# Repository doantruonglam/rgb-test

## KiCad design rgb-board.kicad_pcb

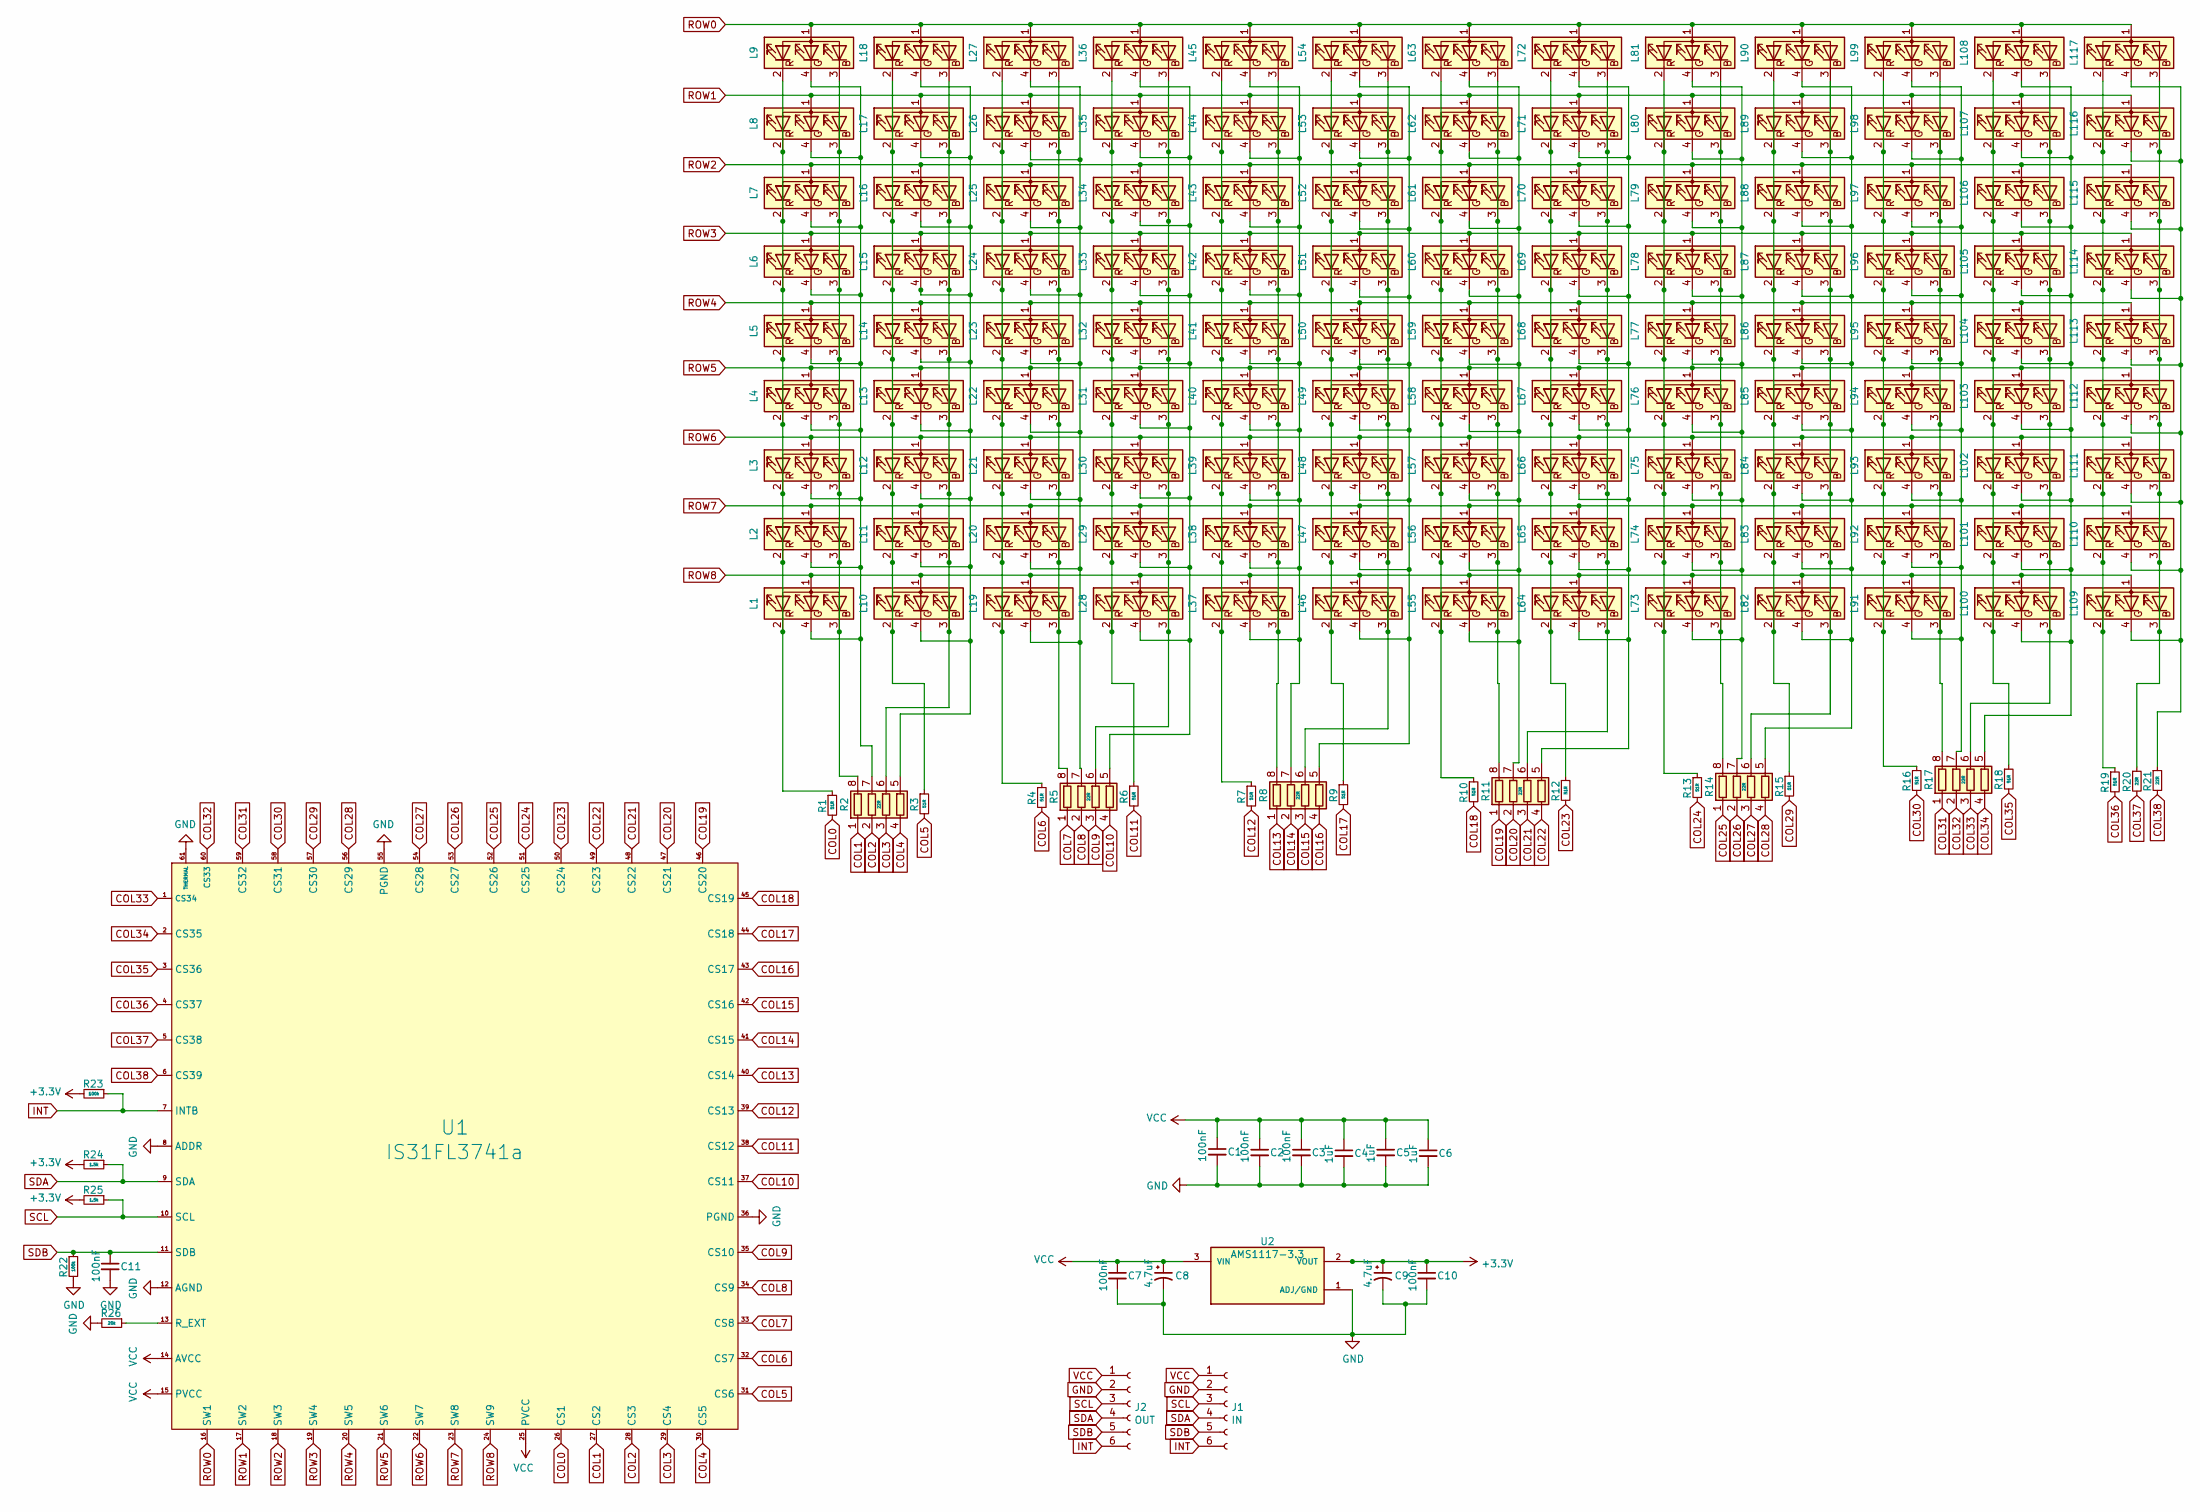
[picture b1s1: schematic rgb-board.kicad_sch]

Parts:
C1, C2, C3, C7, C10, C11: 100nF; C_0805_2012Metric
C4, C5, C6: 1uF; C_0805_2012Metric
C8, C9: 4.7uF; C_0805_2012Metric
J1: IN; PinHeader_1x06_P1.00mm_Vertical
J2: OUT; PinHeader_1x06_P1.00mm_Vertical
L1, L2, L3, L4, L5, L6, L7, L8, L9, L10, L11, L12, L13, L14, L15, L16, L17, L18, L19, L20, L21, L22, L23, L24, L25, L26, L27, L28, L29, L30, L31, L32, L33, L34, L35, L36, L37, L38, L39, L40, L41, L42, L43, L44, L45, L46, L47, L48, L49, L50, L51, L52, L53, L54, L55, L56, L57, L58, L59, L60, L61, L62, L63, L64, L65, L66, L67, L68, L69, L70, L71, L72, L73, L74, L75, L76, L77, L78, L79, L80, L81, L82, L83, L84, L85, L86, L87, L88, L89, L90, L91, L92, L93, L94, L95, L96, L97, L98, L99, L100, L101, L102, L103, L104, L105, L106, L107, L108, L109, L110, L111, L112, L113, L114, L115, L116, L117: LED_ARBG; DIOSC160X150X35-4N
R1, R3, R4, R6, R7, R9, R10, R12, R13, R15, R16, R18, R19: 51R; R_0603_1608Metric
R2, R5, R8, R11, R14, R17: 22R; R_Array_Convex_4x0603
R20, R21: 22R; R_0603_1608Metric
R22, R23: 100k; R_0603_1608Metric
R24, R25: 1.5k; R_0603_1608Metric
R26: 20k; R_0603_1608Metric
U1: IS31FL3741a; QFN-60-1EP_7x7mm_P0.4mm_EP5.4x5.4mm_ThermalReliefs; Manufacturer Part Number IS31FL3741A
U2: AMS1117-3.3; SOT-223-3_TabPin2

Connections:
+3V3: C9.1, C10.1, R23.2, R24.2, R25.2, U2.2 (VOUT)
COL0: R1.2, U1.26 (CS1)
COL1: R2.1 (R1.1), U1.27 (CS2)
COL2: R2.2 (R2.1), U1.28 (CS3)
COL3: R2.3 (R3.1), U1.29 (CS4)
COL4: R2.4 (R4.1), U1.30 (CS5)
COL5: R3.2, U1.31 (CS6)
COL6: R4.2, U1.32 (CS7)
COL7: R5.1 (R1.1), U1.33 (CS8)
COL8: R5.2 (R2.1), U1.34 (CS9)
COL9: R5.3 (R3.1), U1.35 (CS10)
COL10: R5.4 (R4.1), U1.37 (CS11)
COL11: R6.2, U1.38 (CS12)
COL12: R7.2, U1.39 (CS13)
COL13: R8.1 (R1.1), U1.40 (CS14)
COL14: R8.2 (R2.1), U1.41 (CS15)
COL15: R8.3 (R3.1), U1.42 (CS16)
COL16: R8.4 (R4.1), U1.43 (CS17)
COL17: R9.2, U1.44 (CS18)
COL18: R10.2, U1.45 (CS19)
COL19: R11.1 (R1.1), U1.46 (CS20)
COL20: R11.2 (R2.1), U1.47 (CS21)
COL21: R11.3 (R3.1), U1.48 (CS22)
COL22: R11.4 (R4.1), U1.49 (CS23)
COL23: R12.2, U1.50 (CS24)
COL24: R13.2, U1.51 (CS25)
COL25: R14.1 (R1.1), U1.52 (CS26)
COL26: R14.2 (R2.1), U1.53 (CS27)
COL27: R14.3 (R3.1), U1.54 (CS28)
COL28: R14.4 (R4.1), U1.56 (CS29)
COL29: R15.2, U1.57 (CS30)
COL30: R16.2, U1.58 (CS31)
COL31: R17.1 (R1.1), U1.59 (CS32)
COL32: R17.2 (R2.1), U1.60 (CS33)
COL33: R17.3 (R3.1), U1.1 (CS34)
COL34: R17.4 (R4.1), U1.2 (CS35)
COL35: R18.2, U1.3 (CS36)
COL36: R19.2, U1.4 (CS37)
COL37: R20.2, U1.5 (CS38)
COL38: R21.2, U1.6 (CS39)
GND: C1.2, C2.2, C3.2, C4.2, C5.2, C6.2, C7.2, C8.2, C9.2, C10.2, C11.2, J1.2, J2.2, R22.2, R26.2, U1.8 (ADDR), U1.12 (AGND), U1.36 (PGND), U1.55 (PGND), U1.61 (THERMAL), U2.1 (ADJ/GND)
INT: J1.6, J2.6, R23.1, U1.7 (INTB)
unnamed: L1.2 (RK), L2.2 (RK), L3.2 (RK), L4.2 (RK), L5.2 (RK), L6.2 (RK), L7.2 (RK), L8.2 (RK), L9.2 (RK), R1.1
unnamed: L1.3 (BK), L2.3 (BK), L3.3 (BK), L4.3 (BK), L5.3 (BK), L6.3 (BK), L7.3 (BK), L8.3 (BK), L9.3 (BK), R2.8 (R1.2)
unnamed: L1.4 (GK), L2.4 (GK), L3.4 (GK), L4.4 (GK), L5.4 (GK), L6.4 (GK), L7.4 (GK), L8.4 (GK), L9.4 (GK), R2.7 (R2.2)
unnamed: L10.2 (RK), L11.2 (RK), L12.2 (RK), L13.2 (RK), L14.2 (RK), L15.2 (RK), L16.2 (RK), L17.2 (RK), L18.2 (RK), R3.1
unnamed: L10.3 (BK), L11.3 (BK), L12.3 (BK), L13.3 (BK), L14.3 (BK), L15.3 (BK), L16.3 (BK), L17.3 (BK), L18.3 (BK), R2.6 (R3.2)
unnamed: L10.4 (GK), L11.4 (GK), L12.4 (GK), L13.4 (GK), L14.4 (GK), L15.4 (GK), L16.4 (GK), L17.4 (GK), L18.4 (GK), R2.5 (R4.2)
unnamed: L19.2 (RK), L20.2 (RK), L21.2 (RK), L22.2 (RK), L23.2 (RK), L24.2 (RK), L25.2 (RK), L26.2 (RK), L27.2 (RK), R4.1
unnamed: L19.3 (BK), L20.3 (BK), L21.3 (BK), L22.3 (BK), L23.3 (BK), L24.3 (BK), L25.3 (BK), L26.3 (BK), L27.3 (BK), R5.8 (R1.2)
unnamed: L19.4 (GK), L20.4 (GK), L21.4 (GK), L22.4 (GK), L23.4 (GK), L24.4 (GK), L25.4 (GK), L26.4 (GK), L27.4 (GK), R5.7 (R2.2)
unnamed: L28.2 (RK), L29.2 (RK), L30.2 (RK), L31.2 (RK), L32.2 (RK), L33.2 (RK), L34.2 (RK), L35.2 (RK), L36.2 (RK), R6.1
unnamed: L28.3 (BK), L29.3 (BK), L30.3 (BK), L31.3 (BK), L32.3 (BK), L33.3 (BK), L34.3 (BK), L35.3 (BK), L36.3 (BK), R5.6 (R3.2)
unnamed: L28.4 (GK), L29.4 (GK), L30.4 (GK), L31.4 (GK), L32.4 (GK), L33.4 (GK), L34.4 (GK), L35.4 (GK), L36.4 (GK), R5.5 (R4.2)
unnamed: L37.2 (RK), L38.2 (RK), L39.2 (RK), L40.2 (RK), L41.2 (RK), L42.2 (RK), L43.2 (RK), L44.2 (RK), L45.2 (RK), R7.1
unnamed: L37.3 (BK), L38.3 (BK), L39.3 (BK), L40.3 (BK), L41.3 (BK), L42.3 (BK), L43.3 (BK), L44.3 (BK), L45.3 (BK), R8.8 (R1.2)
unnamed: L37.4 (GK), L38.4 (GK), L39.4 (GK), L40.4 (GK), L41.4 (GK), L42.4 (GK), L43.4 (GK), L44.4 (GK), L45.4 (GK), R8.7 (R2.2)
unnamed: L46.2 (RK), L47.2 (RK), L48.2 (RK), L49.2 (RK), L50.2 (RK), L51.2 (RK), L52.2 (RK), L53.2 (RK), L54.2 (RK), R9.1
unnamed: L46.3 (BK), L47.3 (BK), L48.3 (BK), L49.3 (BK), L50.3 (BK), L51.3 (BK), L52.3 (BK), L53.3 (BK), L54.3 (BK), R8.6 (R3.2)
unnamed: L46.4 (GK), L47.4 (GK), L48.4 (GK), L49.4 (GK), L50.4 (GK), L51.4 (GK), L52.4 (GK), L53.4 (GK), L54.4 (GK), R8.5 (R4.2)
unnamed: L55.2 (RK), L56.2 (RK), L57.2 (RK), L58.2 (RK), L59.2 (RK), L60.2 (RK), L61.2 (RK), L62.2 (RK), L63.2 (RK), R10.1
unnamed: L55.3 (BK), L56.3 (BK), L57.3 (BK), L58.3 (BK), L59.3 (BK), L60.3 (BK), L61.3 (BK), L62.3 (BK), L63.3 (BK), R11.8 (R1.2)
unnamed: L55.4 (GK), L56.4 (GK), L57.4 (GK), L58.4 (GK), L59.4 (GK), L60.4 (GK), L61.4 (GK), L62.4 (GK), L63.4 (GK), R11.7 (R2.2)
unnamed: L64.2 (RK), L65.2 (RK), L66.2 (RK), L67.2 (RK), L68.2 (RK), L69.2 (RK), L70.2 (RK), L71.2 (RK), L72.2 (RK), R12.1
unnamed: L64.3 (BK), L65.3 (BK), L66.3 (BK), L67.3 (BK), L68.3 (BK), L69.3 (BK), L70.3 (BK), L71.3 (BK), L72.3 (BK), R11.6 (R3.2)
unnamed: L64.4 (GK), L65.4 (GK), L66.4 (GK), L67.4 (GK), L68.4 (GK), L69.4 (GK), L70.4 (GK), L71.4 (GK), L72.4 (GK), R11.5 (R4.2)
unnamed: L73.2 (RK), L74.2 (RK), L75.2 (RK), L76.2 (RK), L77.2 (RK), L78.2 (RK), L79.2 (RK), L80.2 (RK), L81.2 (RK), R13.1
unnamed: L73.3 (BK), L74.3 (BK), L75.3 (BK), L76.3 (BK), L77.3 (BK), L78.3 (BK), L79.3 (BK), L80.3 (BK), L81.3 (BK), R14.8 (R1.2)
unnamed: L73.4 (GK), L74.4 (GK), L75.4 (GK), L76.4 (GK), L77.4 (GK), L78.4 (GK), L79.4 (GK), L80.4 (GK), L81.4 (GK), R14.7 (R2.2)
unnamed: L82.2 (RK), L83.2 (RK), L84.2 (RK), L85.2 (RK), L86.2 (RK), L87.2 (RK), L88.2 (RK), L89.2 (RK), L90.2 (RK), R15.1
unnamed: L82.3 (BK), L83.3 (BK), L84.3 (BK), L85.3 (BK), L86.3 (BK), L87.3 (BK), L88.3 (BK), L89.3 (BK), L90.3 (BK), R14.6 (R3.2)
unnamed: L82.4 (GK), L83.4 (GK), L84.4 (GK), L85.4 (GK), L86.4 (GK), L87.4 (GK), L88.4 (GK), L89.4 (GK), L90.4 (GK), R14.5 (R4.2)
unnamed: L91.2 (RK), L92.2 (RK), L93.2 (RK), L94.2 (RK), L95.2 (RK), L96.2 (RK), L97.2 (RK), L98.2 (RK), L99.2 (RK), R16.1
unnamed: L91.3 (BK), L92.3 (BK), L93.3 (BK), L94.3 (BK), L95.3 (BK), L96.3 (BK), L97.3 (BK), L98.3 (BK), L99.3 (BK), R17.8 (R1.2)
unnamed: L91.4 (GK), L92.4 (GK), L93.4 (GK), L94.4 (GK), L95.4 (GK), L96.4 (GK), L97.4 (GK), L98.4 (GK), L99.4 (GK), R17.7 (R2.2)
unnamed: L100.2 (RK), L101.2 (RK), L102.2 (RK), L103.2 (RK), L104.2 (RK), L105.2 (RK), L106.2 (RK), L107.2 (RK), L108.2 (RK), R18.1
unnamed: L100.3 (BK), L101.3 (BK), L102.3 (BK), L103.3 (BK), L104.3 (BK), L105.3 (BK), L106.3 (BK), L107.3 (BK), L108.3 (BK), R17.6 (R3.2)
unnamed: L100.4 (GK), L101.4 (GK), L102.4 (GK), L103.4 (GK), L104.4 (GK), L105.4 (GK), L106.4 (GK), L107.4 (GK), L108.4 (GK), R17.5 (R4.2)
unnamed: L109.2 (RK), L110.2 (RK), L111.2 (RK), L112.2 (RK), L113.2 (RK), L114.2 (RK), L115.2 (RK), L116.2 (RK), L117.2 (RK), R19.1
unnamed: L109.3 (BK), L110.3 (BK), L111.3 (BK), L112.3 (BK), L113.3 (BK), L114.3 (BK), L115.3 (BK), L116.3 (BK), L117.3 (BK), R20.1
unnamed: L109.4 (GK), L110.4 (GK), L111.4 (GK), L112.4 (GK), L113.4 (GK), L114.4 (GK), L115.4 (GK), L116.4 (GK), L117.4 (GK), R21.1
unnamed: R26.1, U1.13 (R_EXT)
ROW0: L9.1 (A), L18.1 (A), L27.1 (A), L36.1 (A), L45.1 (A), L54.1 (A), L63.1 (A), L72.1 (A), L81.1 (A), L90.1 (A), L99.1 (A), L108.1 (A), L117.1 (A), U1.16 (SW1)
ROW1: L8.1 (A), L17.1 (A), L26.1 (A), L35.1 (A), L44.1 (A), L53.1 (A), L62.1 (A), L71.1 (A), L80.1 (A), L89.1 (A), L98.1 (A), L107.1 (A), L116.1 (A), U1.17 (SW2)
ROW2: L7.1 (A), L16.1 (A), L25.1 (A), L34.1 (A), L43.1 (A), L52.1 (A), L61.1 (A), L70.1 (A), L79.1 (A), L88.1 (A), L97.1 (A), L106.1 (A), L115.1 (A), U1.18 (SW3)
ROW3: L6.1 (A), L15.1 (A), L24.1 (A), L33.1 (A), L42.1 (A), L51.1 (A), L60.1 (A), L69.1 (A), L78.1 (A), L87.1 (A), L96.1 (A), L105.1 (A), L114.1 (A), U1.19 (SW4)
ROW4: L5.1 (A), L14.1 (A), L23.1 (A), L32.1 (A), L41.1 (A), L50.1 (A), L59.1 (A), L68.1 (A), L77.1 (A), L86.1 (A), L95.1 (A), L104.1 (A), L113.1 (A), U1.20 (SW5)
ROW5: L4.1 (A), L13.1 (A), L22.1 (A), L31.1 (A), L40.1 (A), L49.1 (A), L58.1 (A), L67.1 (A), L76.1 (A), L85.1 (A), L94.1 (A), L103.1 (A), L112.1 (A), U1.21 (SW6)
ROW6: L3.1 (A), L12.1 (A), L21.1 (A), L30.1 (A), L39.1 (A), L48.1 (A), L57.1 (A), L66.1 (A), L75.1 (A), L84.1 (A), L93.1 (A), L102.1 (A), L111.1 (A), U1.22 (SW7)
ROW7: L2.1 (A), L11.1 (A), L20.1 (A), L29.1 (A), L38.1 (A), L47.1 (A), L56.1 (A), L65.1 (A), L74.1 (A), L83.1 (A), L92.1 (A), L101.1 (A), L110.1 (A), U1.23 (SW8)
ROW8: L1.1 (A), L10.1 (A), L19.1 (A), L28.1 (A), L37.1 (A), L46.1 (A), L55.1 (A), L64.1 (A), L73.1 (A), L82.1 (A), L91.1 (A), L100.1 (A), L109.1 (A), U1.24 (SW9)
SCL: J1.3, J2.3, R25.1, U1.10 (SCL)
SDA: J1.4, J2.4, R24.1, U1.9 (SDA)
SDB: C11.1, J1.5, J2.5, R22.1, U1.11 (SDB)
VCC: C1.1, C2.1, C3.1, C4.1, C5.1, C6.1, C7.1, C8.1, J1.1, J2.1, U1.14 (AVCC), U1.15 (PVCC), U1.25 (PVCC), U2.3 (VIN)

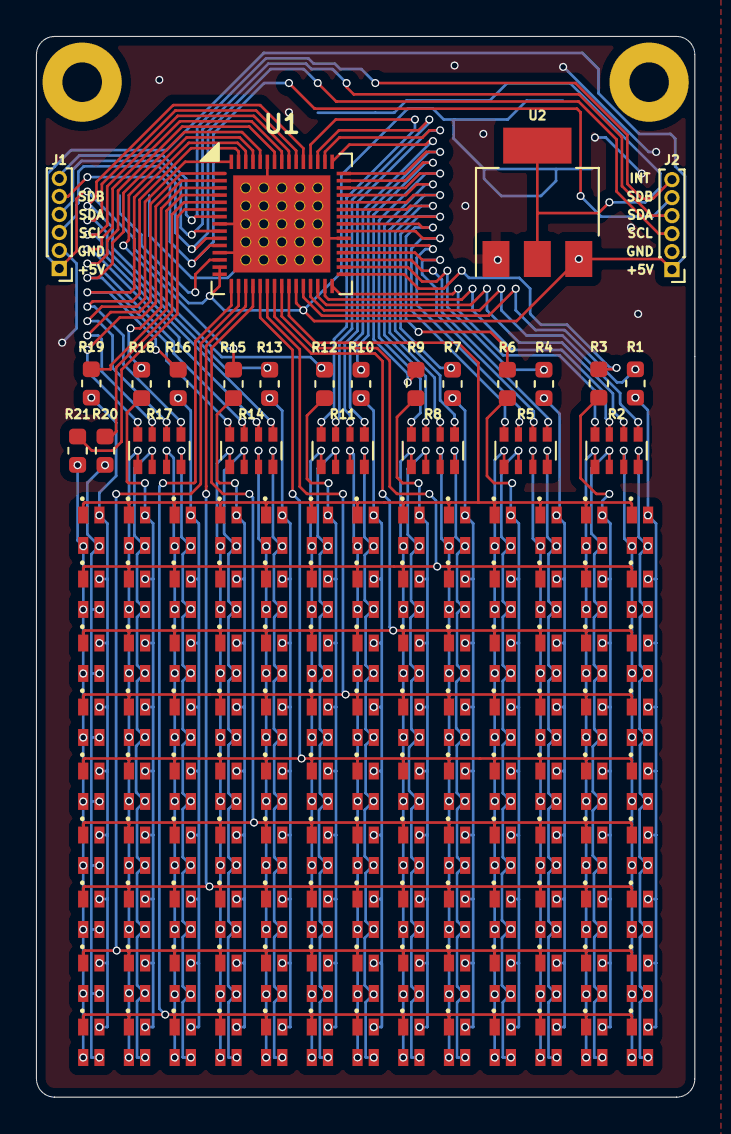
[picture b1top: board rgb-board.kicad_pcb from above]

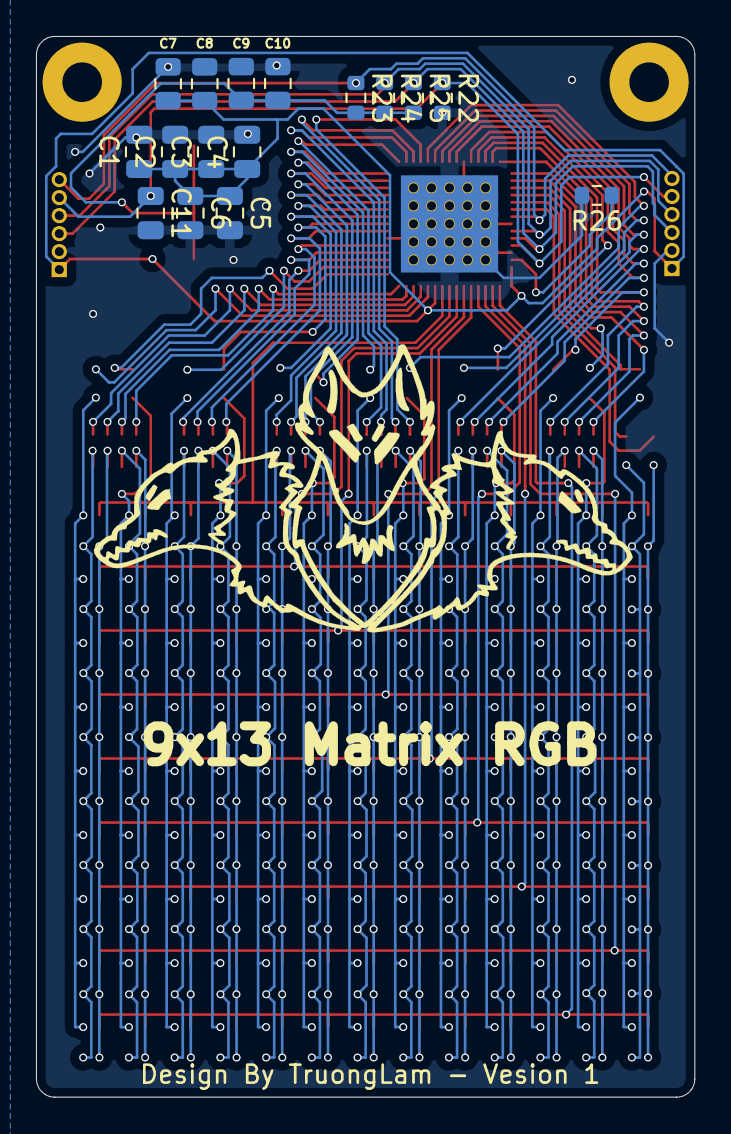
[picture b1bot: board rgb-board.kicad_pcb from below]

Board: 2 copper layers, 36.6 x 58.9 mm, 160 parts (16 on the bottom side), 95 nets.

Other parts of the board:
MM1, MM2: MountingHole_2.2mm_M2_Pad

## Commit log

2022-03-19 init
